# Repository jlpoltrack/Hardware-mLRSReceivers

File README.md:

# Hardware-mLRSReceivers

[mLRS](https://github.com/olliw42/mLRS) receiver boards with CAN, designed in KiCad 10.

| Board | What it is |
|---|---|
| <br>[F1-CAN-Receiver](F1-CAN-Receiver) | STM32F103 + dual E28 (SX1281), 2.4 GHz CAN |
| <br>[RP-mLRS](RP-mLRS) | RP2354A + NiceRF LR2021, CAN or CAN FD, USB-C |

Each board folder has its KiCad project, schematic PDF, renders and JLCPCB production files.

## License

[MIT](LICENSE)

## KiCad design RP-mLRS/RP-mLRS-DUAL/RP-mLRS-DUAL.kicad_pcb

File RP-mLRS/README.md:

# RP-mLRS

An [mLRS](https://github.com/olliw42/mLRS) receiver: RP2354A, NiceRF LR2021 (Sub-GHz + 2.4 GHz), two GH-compatible
CAN connectors and USB-C.

One PCB, [`RP-mLRS-DUAL/`](RP-mLRS-DUAL), takes either CAN interface, chosen at assembly:

| Build | CAN interface | Fit | Production files |
|---|---|---|---|
| CANFD | MCP251863 controller + transceiver (SPI0) | U5 | `production-canfd/` |
| CAN | [can2040](https://github.com/KevinOConnor/can2040) (PIO) + SN65HVD230 | U7 | `production-can/` |

## Connectors

**J2, J3 CAN** (CJT A1257WR-S-4P, JST-GH compatible, in parallel): 1 +5V, 2 CANH, 3 CANL, 4 GND.
Bridge **JP1** for 120 Ω termination at a bus end.

**J1 USB-C**: power (through a Schottky) and firmware.

**Test pads**: top C / G / D = SWCLK / GND / SWDIO; bottom TX / RX = UART1, TX1 = UART0 TX, 5V, G.

## Assembly

JLC assembles the top side. U4 (LR2021), C23 and C24 are on the bottom, marked DNP, and soldered by hand.

## Docs

- [docs/FIRMWARE.md](docs/FIRMWARE.md): GPIO map and firmware notes
- [docs/COST-REDUCED.md](docs/COST-REDUCED.md): CAN-build cost notes

## License

[MIT](../LICENSE)

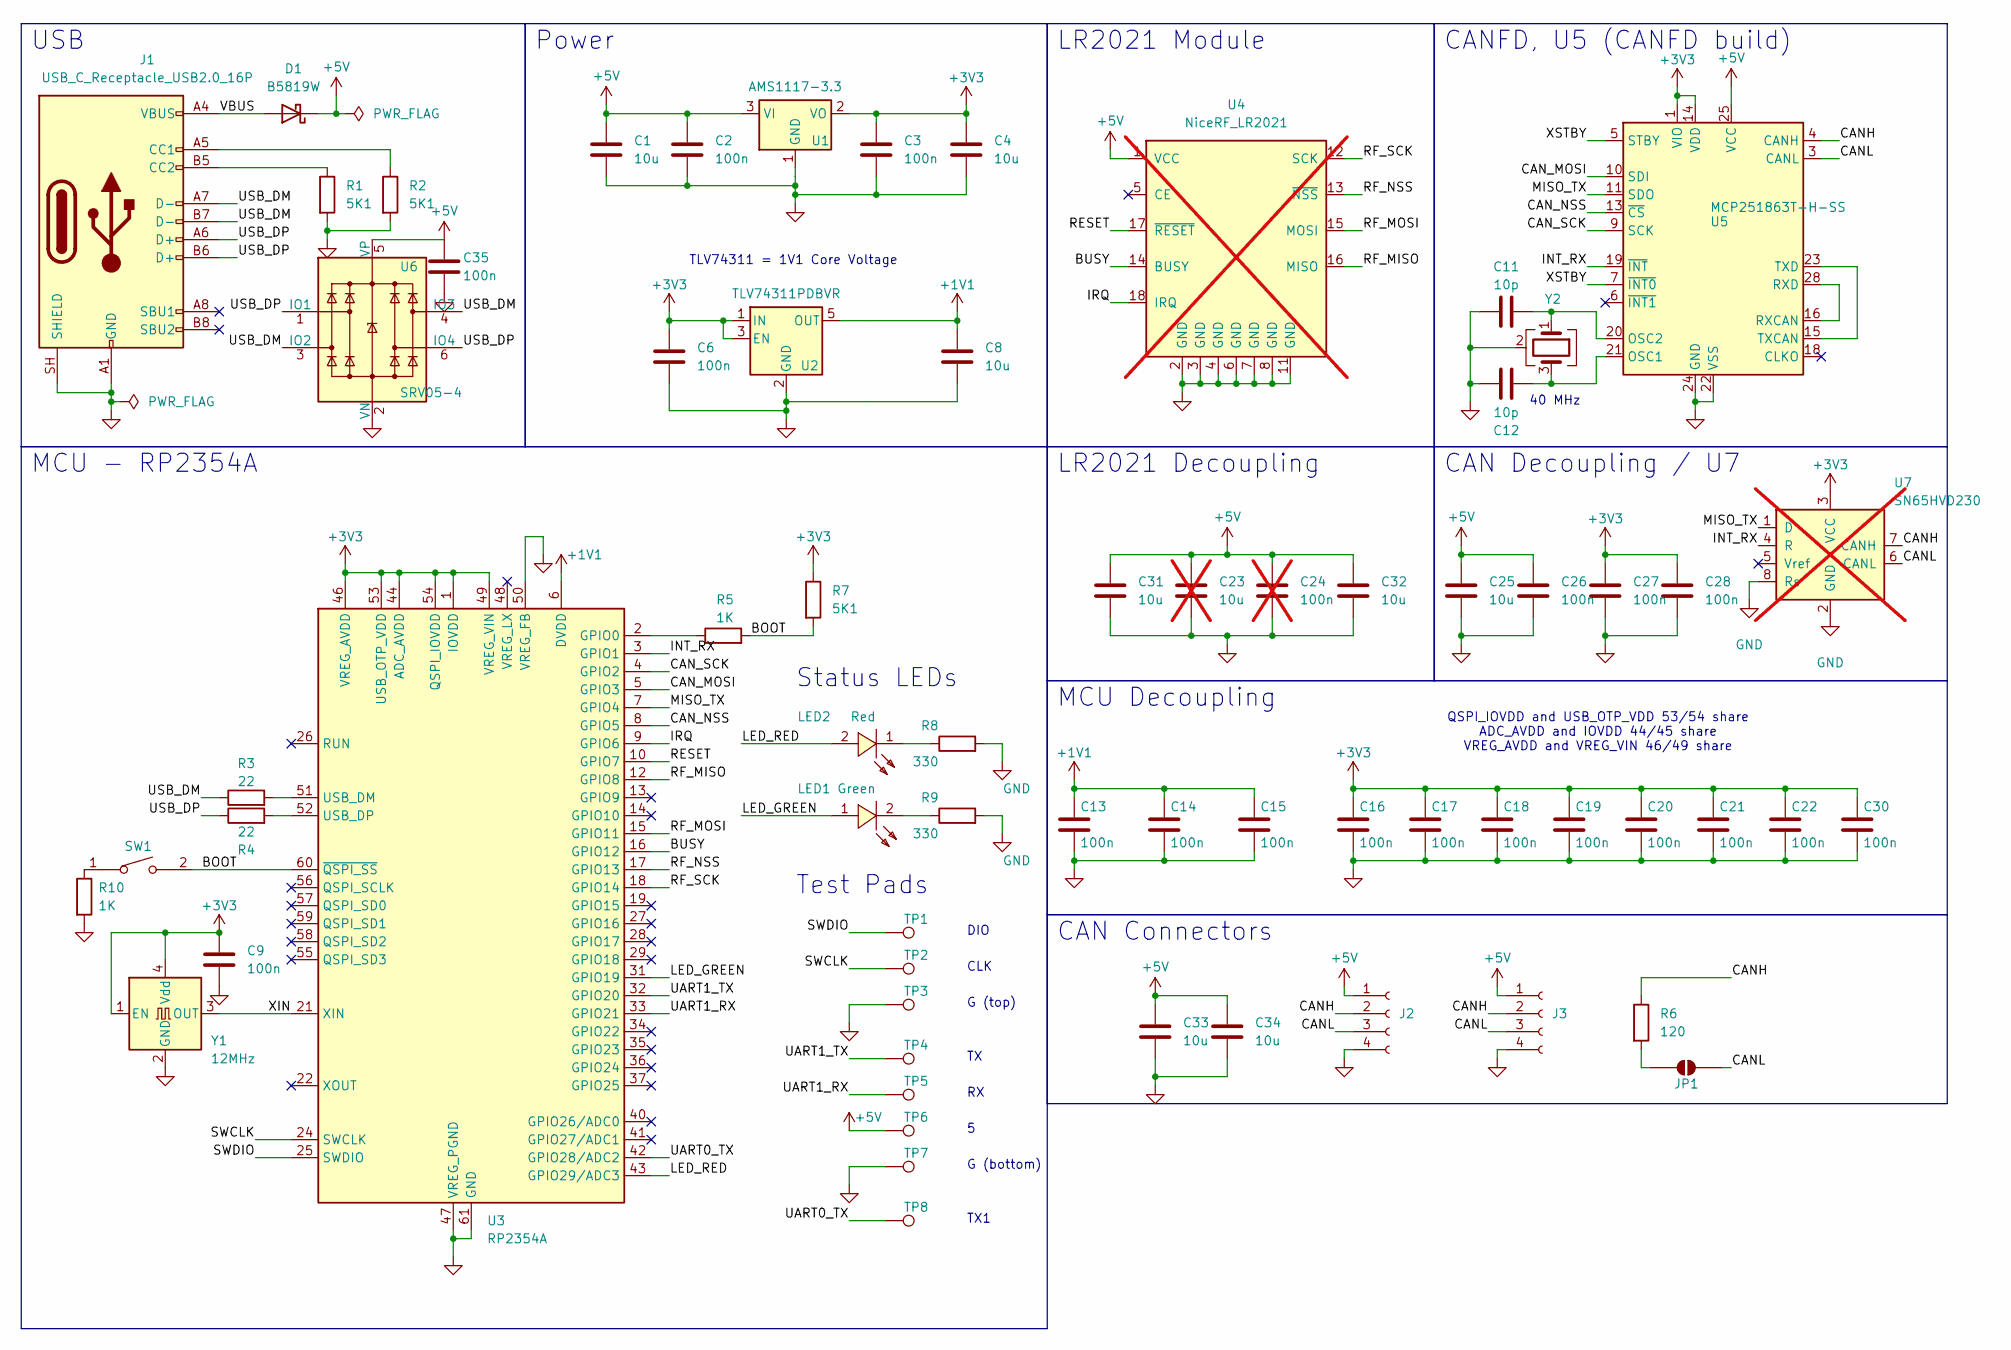
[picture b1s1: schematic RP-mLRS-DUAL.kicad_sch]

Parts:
C1, C4, C8, C25, C31, C32, C33, C34: 10u; C_0603_1608Metric; LCSC C96446
C2, C26, C35: 100n; C_0402_1005Metric; LCSC C307331
C3, C6, C9, C13, C14, C15, C16, C17, C18, C19, C20, C21, C22, C27, C28, C30: 100n; C_0402_1005Metric; LCSC C1525
C11, C12: 10p; C_0402_1005Metric; LCSC C32949
C23: 10u; C_0603_1608Metric_Pad1.08x0.95mm_HandSolder; LCSC C96446; not fitted
C24: 100n; C_0603_1608Metric_Pad1.08x0.95mm_HandSolder; LCSC C14663; not fitted
D1: B5819W; D_SOD-123; LCSC C8598
J1: USB_C_Receptacle_USB2.0_16P; USB_C_Receptacle_HH_16P_Y495; LCSC C52209111
J2, J3: Conn_01x04_Socket; CJT_A1257WR-S-4P_1x04_P1.25mm_Horizontal; LCSC C225127
JP1: SolderJumper_2_Open; SolderJumper-2_P1.3mm_Open_TrianglePad1.0x1.5mm
LED1: Green; LED0805-R-RD_NoSilk; MPN KT-0805G; LCSC Part C2297
LED2: Red; LED0805-RD_NoSilk; MPN FC-2012HRK-620D; LCSC Part C84256
R1, R2, R7: 5K1; R_0402_1005Metric; LCSC C25905
R3, R4: 22; R_0402_1005Metric; LCSC C25092
R5, R10: 1K; R_0402_1005Metric; LCSC C11702
R6: 120; R_0402_1005Metric_Pad0.72x0.64mm_HandSolder; LCSC C25079
R8, R9: 330; R_0402_1005Metric; LCSC C25104
SW1: TS-1088-AR02016; SW-SMD_L3.9-W3.0-P4.45; MPN TS-1088-AR02016; LCSC Part C720477
TP1, TP2, TP3, TP4, TP5, TP6, TP7, TP8: TestPoint; TestPoint_Pad_2.0x2.0mm
U1: AMS1117-3.3; SOT-223-3_TabPin2; LCSC C6186
U2: TLV74311PDBVR; SOT-23-5; LCSC C485147
U3: RP2354A; QFN-60-1EP_7x7mm_P0.4mm_EP3.4x3.4mm_ThermalVias; LCSC C41378174
U4: NiceRF_LR2021; NiceRF_LR2021_NoSilk; not fitted
U5: MCP251863T-H-SS; SSOP-28_5.3x10.2mm_P0.65mm; LCSC C5226885
U6: SRV05-4; SRV05-4_SOT-23-6; LCSC C85364
U7: SN65HVD230; SOIC-8_3.9x4.9mm_P1.27mm; LCSC C12084; not fitted
Y1: 12MHz; Oscillator_SMD_YXC_YSO110TR-4Pin_3.2x2.5mm; LCSC C5280582
Y2: Crystal_GND24; Crystal_SMD_2016-4Pin_2.0x1.6mm; LCSC C20623609

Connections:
+1V1: C8.1, C13.1, C14.1, C15.1, U2.5 (OUT), U3.6 (DVDD), U3.23 (DVDD), U3.39 (DVDD)
+3V3: C3.1, C4.1, C6.1, C9.1, C16.1, C17.1, C18.1, C19.1, C20.1, C21.1, C22.1, C27.1, C28.1, C30.1, R7.1, U1.2 (VO), U2.1 (IN), U2.3 (EN), U3.1 (IOVDD), U3.11 (IOVDD), U3.20 (IOVDD), U3.30 (IOVDD), U3.38 (IOVDD), U3.44 (ADC_AVDD), U3.45 (IOVDD), U3.46 (VREG_AVDD), U3.49 (VREG_VIN), U3.53 (USB_OTP_VDD), U3.54 (QSPI_IOVDD), U5.1 (VIO), U5.14 (VDD), U7.3 (VCC), Y1.1 (EN), Y1.4 (Vdd)
+5V: C1.1, C2.1, C23.1, C24.1, C25.1, C26.1, C31.1, C32.1, C33.1, C34.1, C35.1, D1.1 (K), J2.1, J3.1, TP6.1 (1_1), U1.3 (VI), U4.1 (VCC), U5.25 (VCC), U6.5 (VP)
/BOOT: R5.2, R7.2, SW1.2, U3.60 (~QSPI_SS)
/BUSY: U3.16 (GPIO12), U4.14 (BUSY)
/CANH: J2.2, J3.2, R6.1, U5.4 (CANH), U7.7 (CANH)
/CANL: J2.3, J3.3, JP1.1 (A), U5.3 (CANL), U7.6 (CANL)
/CAN_MOSI: U3.5 (GPIO3), U5.10 (SDI)
/CAN_NSS: U3.8 (GPIO5), U5.13 (~CS)
/CAN_SCK: U3.4 (GPIO2), U5.9 (SCK)
/INT_RX: U3.3 (GPIO1), U5.19 (~INT), U7.4 (R)
/IRQ: U3.9 (GPIO6), U4.18 (IRQ)
/LED_GREEN: LED1.1 (A), U3.31 (GPIO19)
/LED_RED: LED2.2 (+), U3.43 (GPIO29/ADC3)
/MISO_TX: U3.7 (GPIO4), U5.11 (SDO), U7.1 (D)
/RESET: U3.10 (GPIO7), U4.17 (~RESET)
/RF_MISO: U3.12 (GPIO8), U4.16 (MISO)
/RF_MOSI: U3.15 (GPIO11), U4.15 (MOSI)
/RF_NSS: U3.17 (GPIO13), U4.13 (~NSS)
/RF_SCK: U3.18 (GPIO14), U4.12 (SCK)
/SWCLK: TP2.1 (1_1), U3.24 (SWCLK)
/SWDIO: TP1.1 (1_1), U3.25 (SWDIO)
/UART0_TX: TP8.1 (1_1), U3.42 (GPIO28/ADC2)
/UART1_RX: TP5.1 (1_1), U3.33 (GPIO21)
/UART1_TX: TP4.1 (1_1), U3.32 (GPIO20)
/USB_DM: J1.A7 (D-), J1.B7 (D-), R3.1, U6.3 (IO2), U6.4 (IO3)
/USB_DP: J1.A6 (D+), J1.B6 (D+), R4.1, U6.1 (IO1), U6.6 (IO4)
/VBUS: D1.2 (A), J1.A4 (VBUS), J1.A9 (VBUS), J1.B4 (VBUS), J1.B9 (VBUS)
/XIN: U3.21 (XIN), Y1.3 (OUT)
/XSTBY: U5.5 (STBY), U5.7 (~INT0)
GND: C1.2, C2.2, C3.2, C4.2, C6.2, C8.2, C9.2, C11.1, C12.2, C13.2, C14.2, C15.2, C16.2, C17.2, C18.2, C19.2, C20.2, C21.2, C22.2, C23.2, C24.2, C25.2, C26.2, C27.2, C28.2, C30.2, C31.2, C32.2, C33.2, C34.2, C35.2, J1.A1 (GND), J1.A12 (GND), J1.B1 (GND), J1.B12 (GND), J1.SH (SHIELD), J2.4, J3.4, R1.2, R2.2, R8.2, R9.2, R10.2, TP3.1 (1_1), TP7.1 (1_1), U1.1 (GND), U2.2 (GND), U3.47 (VREG_PGND), U3.50 (VREG_FB), U3.61 (GND), U4.2 (GND), U4.3 (GND), U4.4 (GND), U4.6 (GND), U4.7 (GND), U4.8 (GND), U4.11 (GND), U5.22 (VSS), U5.24 (GND), U6.2 (VN), U7.2 (GND), U7.8 (Rs), Y1.2 (GND), Y2.2 (G), Y2.4 (G)
unnamed: J1.A5 (CC1), R2.1
unnamed: J1.B5 (CC2), R1.1
unnamed: JP1.2 (B), R6.2
unnamed: LED1.2 (K), R9.1
unnamed: LED2.1 (-), R8.1
unnamed: R10.1, SW1.1
unnamed: R5.1, U3.2 (GPIO0)
unnamed: R3.2, U3.51 (USB_DM)
unnamed: R4.2, U3.52 (USB_DP)
unnamed: C12.1, U5.21 (OSC1), Y2.3
unnamed: C11.2, U5.20 (OSC2), Y2.1
unnamed: U5.16 (RXCAN), U5.28 (RXD)
unnamed: U5.15 (TXCAN), U5.23 (TXD)

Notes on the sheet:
Power
QSPI_IOVDD and USB_OTP_VDD 53/54 share ADC_AVDD and IOVDD 44/45 share VREG_AVDD and VREG_VIN 46/49 share
CANFD, U5 (CANFD build)
TLV74311 = 1V1 Core Voltage
40 MHz
LR2021 Module
CAN Decoupling / U7
MCU - RP2354A
CAN Connectors
MCU Decoupling
USB
LR2021 Decoupling
Status LEDs
Test Pads
DIO
CLK
G (top)
G (bottom)
TX1

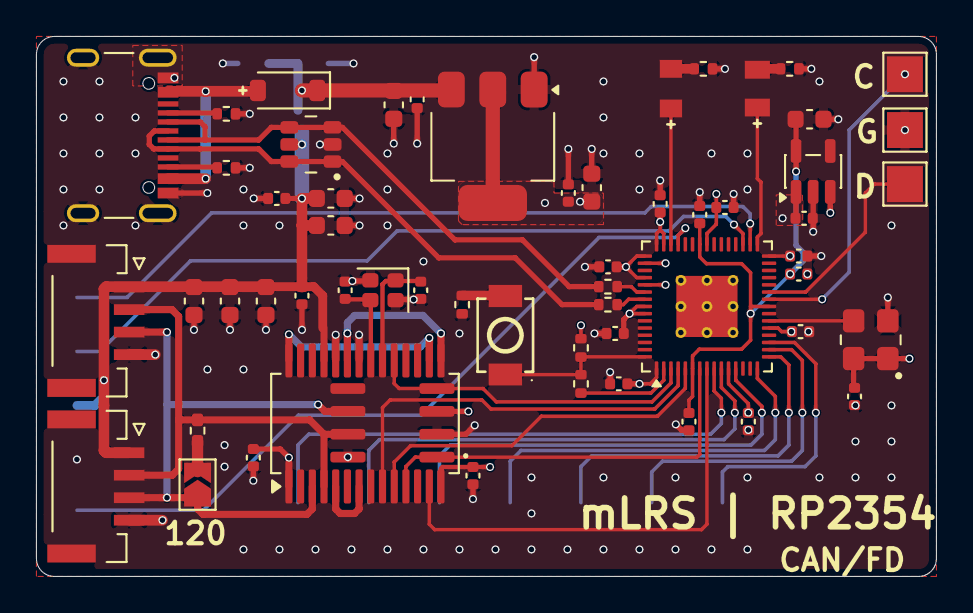
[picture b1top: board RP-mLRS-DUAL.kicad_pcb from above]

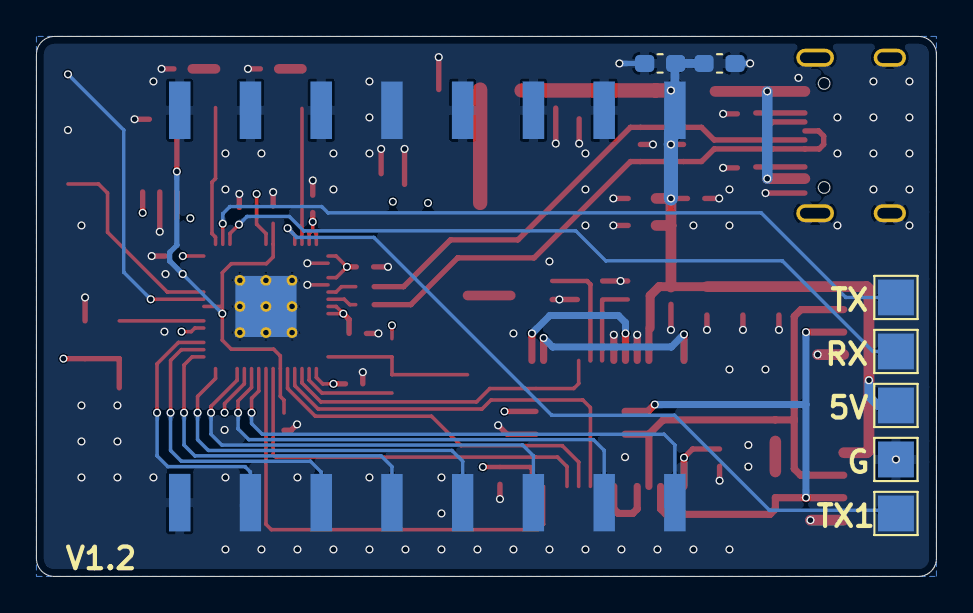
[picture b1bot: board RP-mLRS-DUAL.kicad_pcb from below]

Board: 4 copper layers, 50.0 x 30.0 mm, 68 parts (8 on the bottom side), 44 nets.

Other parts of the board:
LOGO1: mLRS title
LOGO2: title

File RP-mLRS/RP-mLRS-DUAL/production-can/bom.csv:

Designator,Footprint,Quantity,Value,LCSC Part #
"C1, C25, C31, C32, C33, C34, C4, C8",0603,8,10u,C96446
"C11, C12",0402,2,10p,C32949
"C13, C14, C15, C16, C17, C18, C19, C20, C21, C22, C27, C28, C3, C30, C6, C9",0402,16,100n,C1525
"C2, C26, C35",0402,3,100n,C307331
D1,D_SOD-123,1,B5819W,C8598
J1,USB_C_Receptacle_HH_16P_Y495,1,USB_C_Receptacle_USB2.0_16P,C52209111
"J2, J3",CJT_A1257WR-S-4P_1x04_P1.25mm_Horizontal,2,Conn_01x04_Socket,C225127
LED1,LED0805-R-RD_NoSilk,1,Green,C2297
LED2,LED0805-RD_NoSilk,1,Red,C84256
"R1, R2, R7",0402,3,5K1,C25905
"R10, R5",0402,2,1K,C11702
"R3, R4",0402,2,22,C25092
R6,0402,1,120,C25079
"R8, R9",0402,2,330,C25104
SW1,SW-SMD_L3.9-W3.0-P4.45,1,TS-1088-AR02016,C720477
U1,SOT-223-3_TabPin2,1,AMS1117-3.3,C6186
U2,SOT-23-5,1,TLV74311PDBVR,C485147
U3,QFN-60-1EP_7x7mm_P0.4mm_EP3.4x3.4mm_ThermalVias,1,RP2354A,C41378174
U6,SRV05-4_SOT-23-6,1,SRV05-4,C85364
U7,SOIC-8_3.9x4.9mm_P1.27mm,1,SN65HVD230,C12084
Y1,Oscillator_SMD_YXC_YSO110TR-4Pin_3.2x2.5mm,1,12MHz,C5280582
Y2,Crystal_SMD_2016-4Pin_2.0x1.6mm,1,Crystal_GND24,C20623609

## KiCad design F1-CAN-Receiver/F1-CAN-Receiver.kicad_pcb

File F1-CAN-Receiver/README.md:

# F1-CAN-Receiver

An [mLRS](https://github.com/olliw42/mLRS) 2.4 GHz CAN receiver: STM32F103C8T6, two E28-2G4M27S (SX1281) for
diversity, and an SN65HVD230 CAN transceiver, powered from the CAN 5 V. Based on Olli's dual-E28 board02.

## Connectors

**J1, J2 CAN** (CJT A1257WR-S-4P, JST-GH compatible, in parallel): 1 5V, 2 CAN_H, 3 CAN_L, 4 GND. Close **JP1** to terminate.

**Test pads** (bottom): UART1 (5V, TX, RX, G; also the ROM bootloader, hold BOOT0 at power-up), UART2 OUT, SWD, DBG.

## Assembly

JLC assembles the top side. M1 (top), M2 (bottom), C18 and C19 are DNP and soldered by hand; leave M2 off for a single radio.

## Docs

[docs/design.md](docs/design.md): design decisions, pin map, BOM and firmware notes.

## License

[MIT](../LICENSE)

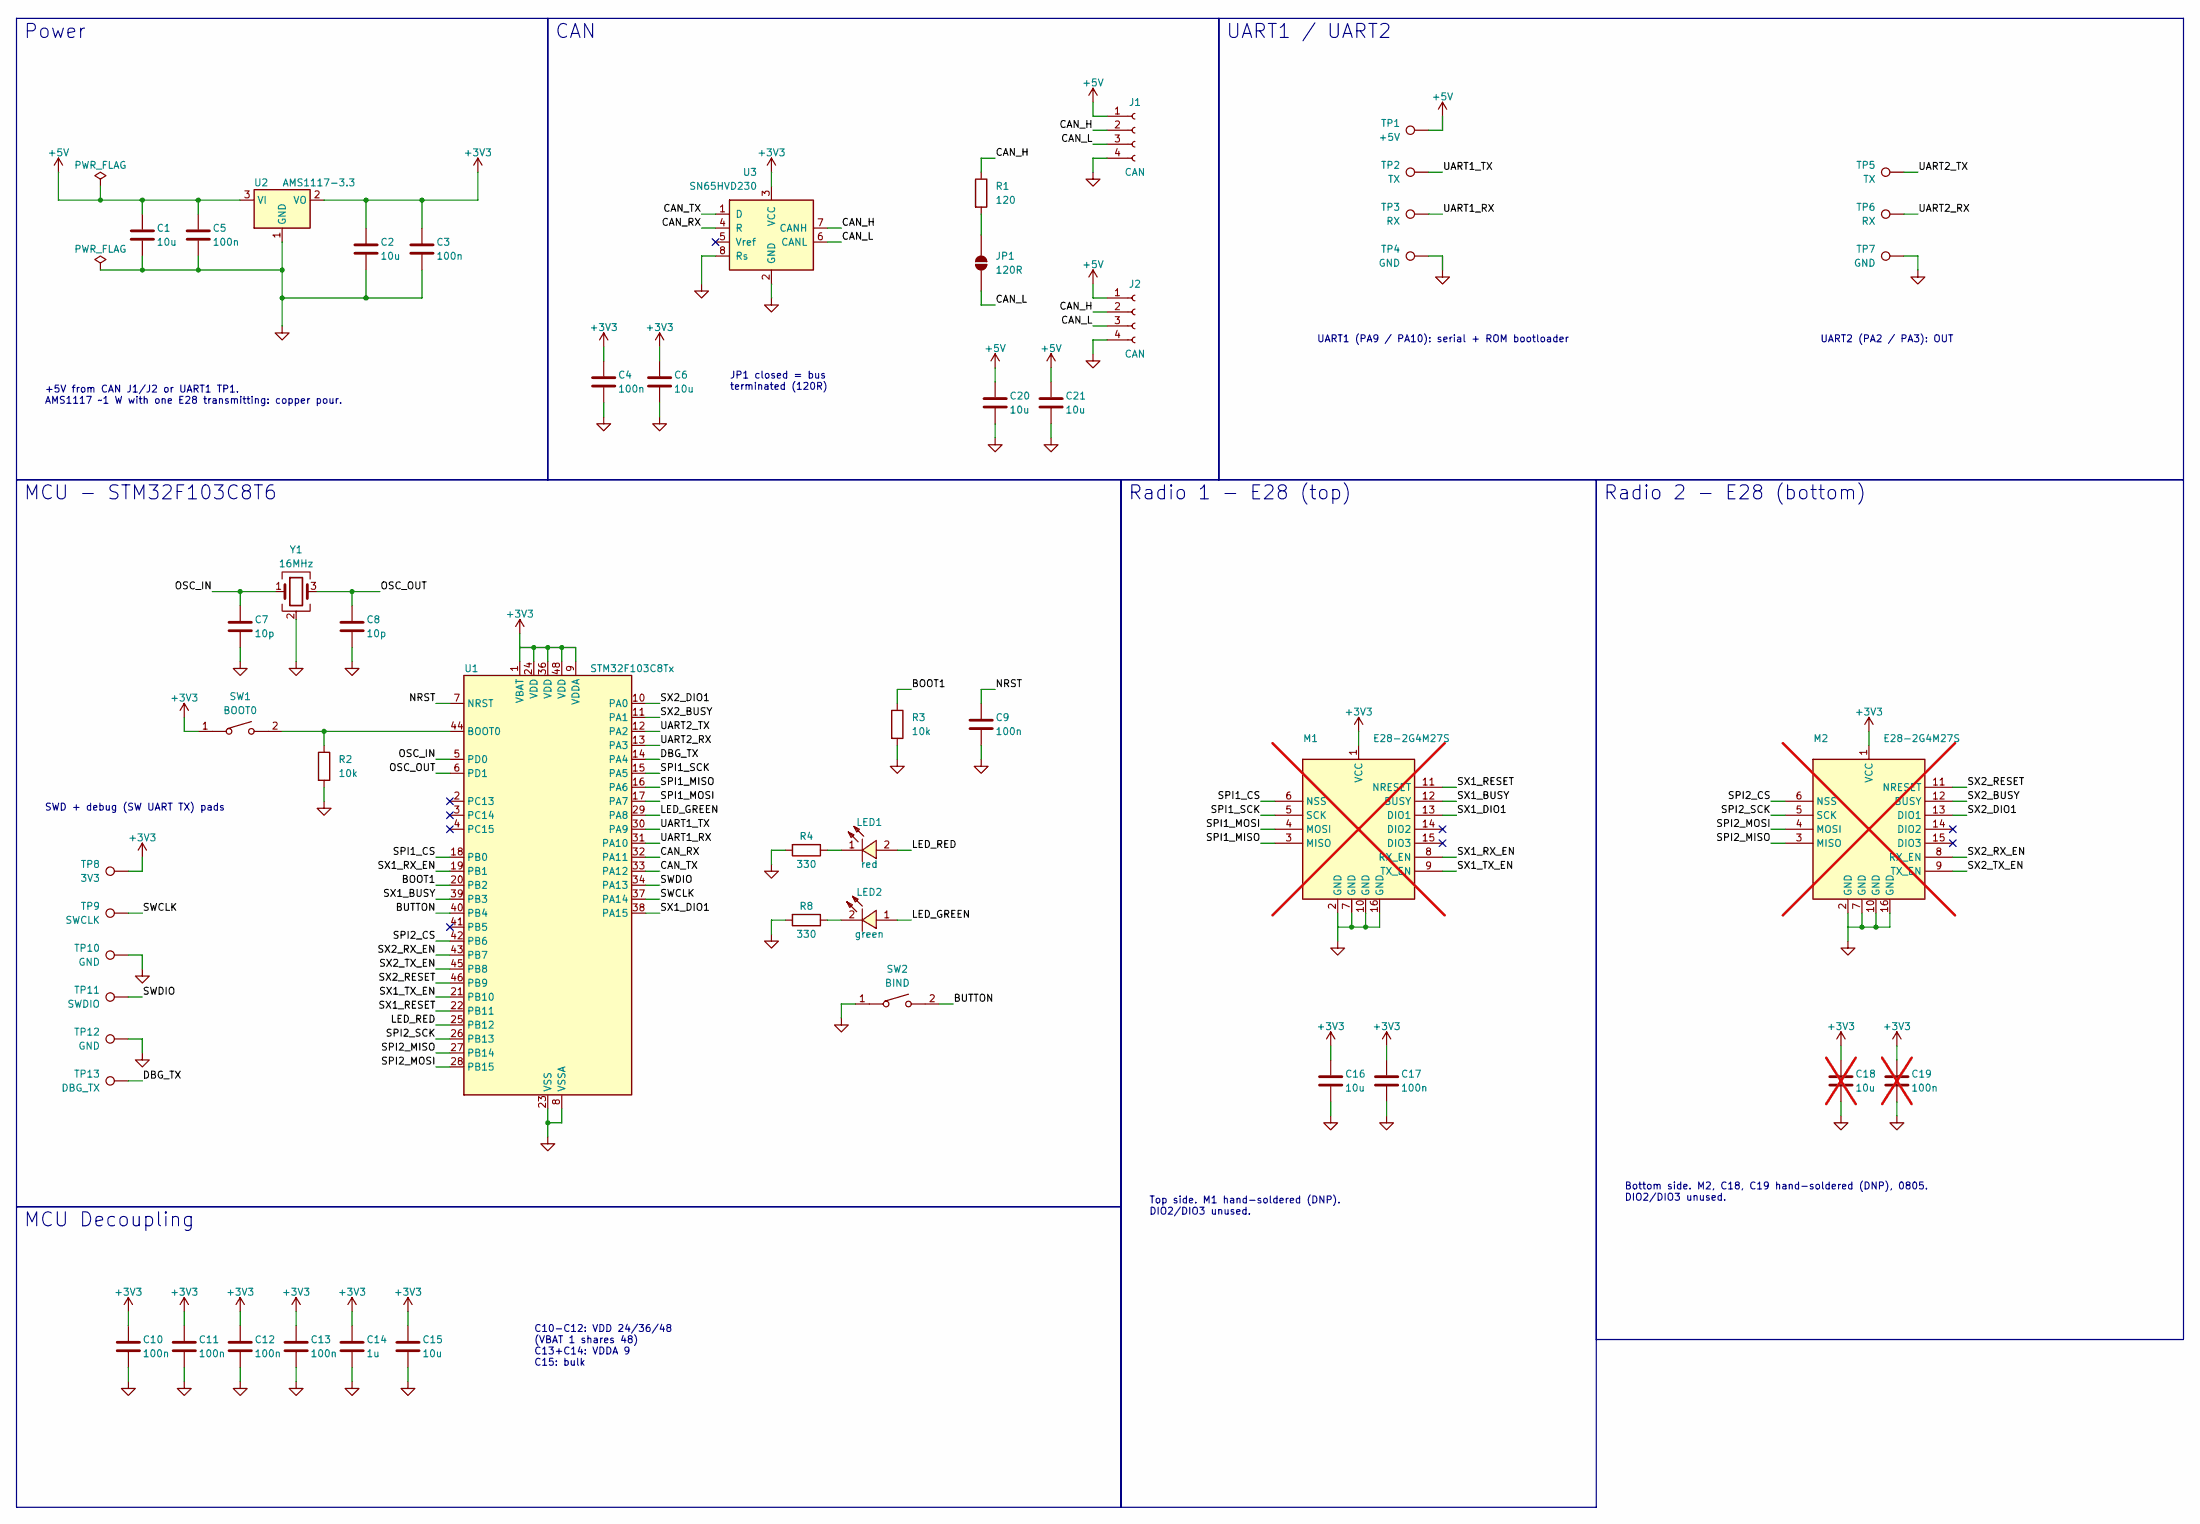
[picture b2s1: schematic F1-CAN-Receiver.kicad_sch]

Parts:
C1, C2, C6, C15, C16, C20, C21: 10u; C_0603_1608Metric; LCSC C96446
C3, C4, C5, C9, C10, C11, C12, C13, C17: 100n; C_0402_1005Metric; LCSC C307331
C7, C8: 10p; C_0402_1005Metric; LCSC C32949
C14: 1u; C_0402_1005Metric; LCSC C52923
C18: 10u; C_0805_2012Metric_Pad1.18x1.45mm_HandSolder; LCSC C15850; not fitted
C19: 100n; C_0805_2012Metric_Pad1.18x1.45mm_HandSolder; LCSC C49678; not fitted
J1, J2: CAN; CJT_A1257WR-S-4P_1x04_P1.25mm_Horizontal; LCSC C225127
JP1: 120R; SolderJumper-2_P1.3mm_Open_TrianglePad1.0x1.5mm
LED1: red; LED0805-RD_NoSilk; MPN NCD0805R1; LCSC C84256
LED2: green; LED0805-R-RD_NoSilk; MPN KT-0805G; LCSC C2297
M1, M2: E28-2G4M27S; LCSC C411312; not fitted
R1: 120; R_0402_1005Metric_Pad0.72x0.64mm_HandSolder; LCSC C25079
R2, R3: 10k; R_0402_1005Metric; LCSC C25744
R4, R8: 330; R_0402_1005Metric; LCSC C25104
SW1: BOOT0; SW-SMD_L3.9-W3.0-P4.45; MPN TS-1088-AR02016; LCSC C720477
SW2: BIND; SW-SMD_L3.9-W3.0-P4.45; MPN TS-1088-AR02016; LCSC C720477
TP1: +5V; TestPoint_Pad_2.0x2.0mm
TP2, TP5: TX; TestPoint_Pad_2.0x2.0mm
TP3, TP6: RX; TestPoint_Pad_2.0x2.0mm
TP4, TP7, TP10, TP12: GND; TestPoint_Pad_2.0x2.0mm
TP8: 3V3; TestPoint_Pad_2.0x2.0mm
TP9: SWCLK; TestPoint_Pad_2.0x2.0mm
TP11: SWDIO; TestPoint_Pad_2.0x2.0mm
TP13: DBG_TX; TestPoint_Pad_2.0x2.0mm
U1: STM32F103C8Tx; LQFP-48_7x7mm_P0.5mm; LCSC C8734
U2: AMS1117-3.3; SOT-223-3_TabPin2; LCSC C6186
U3: SN65HVD230; SOIC-8_3.9x4.9mm_P1.27mm; LCSC C12084
Y1: 16MHz; Crystal_SMD_3225-4Pin_3.2x2.5mm; LCSC C13738

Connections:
+3V3: C2.1, C3.1, C4.1, C6.1, C10.1, C11.1, C12.1, C13.1, C14.1, C15.1, C16.1, C17.1, C18.1, C19.1, M1.1 (VCC), M2.1 (VCC), SW1.1, TP8.1 (1_1), U1.1 (VBAT), U1.9 (VDDA), U1.24 (VDD), U1.36 (VDD), U1.48 (VDD), U2.2 (VO), U3.3 (VCC)
+5V: C1.1, C5.1, C20.1, C21.1, J1.1, J2.1, TP1.1 (1_1), U2.3 (VI)
/BOOT1: R3.1, U1.20 (PB2)
/BUTTON: SW2.2, U1.40 (PB4)
/CAN_H: J1.2, J2.2, R1.1, U3.7 (CANH)
/CAN_L: J1.3, J2.3, JP1.1 (A), U3.6 (CANL)
/CAN_RX: U1.32 (PA11), U3.4 (R)
/CAN_TX: U1.33 (PA12), U3.1 (D)
/DBG_TX: TP13.1 (1_1), U1.14 (PA4)
/LED_GREEN: LED2.1 (A), U1.29 (PA8)
/LED_RED: LED1.2 (+), U1.25 (PB12)
/NRST: C9.1, U1.7 (NRST)
/OSC_IN: C7.1, U1.5 (PD0), Y1.1
/OSC_OUT: C8.1, U1.6 (PD1), Y1.3
/SPI1_CS: M1.6 (NSS), U1.18 (PB0)
/SPI1_MISO: M1.3 (MISO), U1.16 (PA6)
/SPI1_MOSI: M1.4 (MOSI), U1.17 (PA7)
/SPI1_SCK: M1.5 (SCK), U1.15 (PA5)
/SPI2_CS: M2.6 (NSS), U1.42 (PB6)
/SPI2_MISO: M2.3 (MISO), U1.27 (PB14)
/SPI2_MOSI: M2.4 (MOSI), U1.28 (PB15)
/SPI2_SCK: M2.5 (SCK), U1.26 (PB13)
/SWCLK: TP9.1 (1_1), U1.37 (PA14)
/SWDIO: TP11.1 (1_1), U1.34 (PA13)
/SX1_BUSY: M1.12 (BUSY), U1.39 (PB3)
/SX1_DIO1: M1.13 (DIO1), U1.38 (PA15)
/SX1_RESET: M1.11 (NRESET), U1.22 (PB11)
/SX1_RX_EN: M1.8 (RX_EN), U1.19 (PB1)
/SX1_TX_EN: M1.9 (TX_EN), U1.21 (PB10)
/SX2_BUSY: M2.12 (BUSY), U1.11 (PA1)
/SX2_DIO1: M2.13 (DIO1), U1.10 (PA0)
/SX2_RESET: M2.11 (NRESET), U1.46 (PB9)
/SX2_RX_EN: M2.8 (RX_EN), U1.43 (PB7)
/SX2_TX_EN: M2.9 (TX_EN), U1.45 (PB8)
/UART1_RX: TP3.1 (1_1), U1.31 (PA10)
/UART1_TX: TP2.1 (1_1), U1.30 (PA9)
/UART2_RX: TP6.1 (1_1), U1.13 (PA3)
/UART2_TX: TP5.1 (1_1), U1.12 (PA2)
GND: C1.2, C2.2, C3.2, C4.2, C5.2, C6.2, C7.2, C8.2, C9.2, C10.2, C11.2, C12.2, C13.2, C14.2, C15.2, C16.2, C17.2, C18.2, C19.2, C20.2, C21.2, J1.4, J2.4, M1.2 (GND), M1.7 (GND), M1.10 (GND), M1.16 (GND), M2.2 (GND), M2.7 (GND), M2.10 (GND), M2.16 (GND), R2.2, R3.2, R4.2, R8.2, SW2.1, TP4.1 (1_1), TP7.1 (1_1), TP10.1 (1_1), TP12.1 (1_1), U1.8 (VSSA), U1.23 (VSS), U1.35 (VSS), U1.47 (VSS), U2.1 (GND), U3.2 (GND), U3.8 (Rs), Y1.2 (G), Y1.4 (G)
unnamed: JP1.2 (B), R1.2
unnamed: LED1.1 (-), R4.1
unnamed: LED2.2 (K), R8.1
unnamed: R2.1, SW1.2, U1.44 (BOOT0)

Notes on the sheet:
Power
CAN
UART1 / UART2
MCU - STM32F103C8T6
MCU Decoupling
Radio 1 - E28 (top)
Radio 2 - E28 (bottom)
+5V from CAN J1/J2 or UART1 TP1. AMS1117 ~1 W with one E28 transmitting: copper pour.
JP1 closed = bus terminated (120R)
UART1 (PA9 / PA10): serial + ROM bootloader
UART2 (PA2 / PA3): OUT
SWD + debug (SW UART TX) pads
C10-C12: VDD 24/36/48 (VBAT 1 shares 48) C13+C14: VDDA 9 C15: bulk
Top side. M1 hand-soldered (DNP). DIO2/DIO3 unused.
Bottom side. M2, C18, C19 hand-soldered (DNP), 0805. DIO2/DIO3 unused.

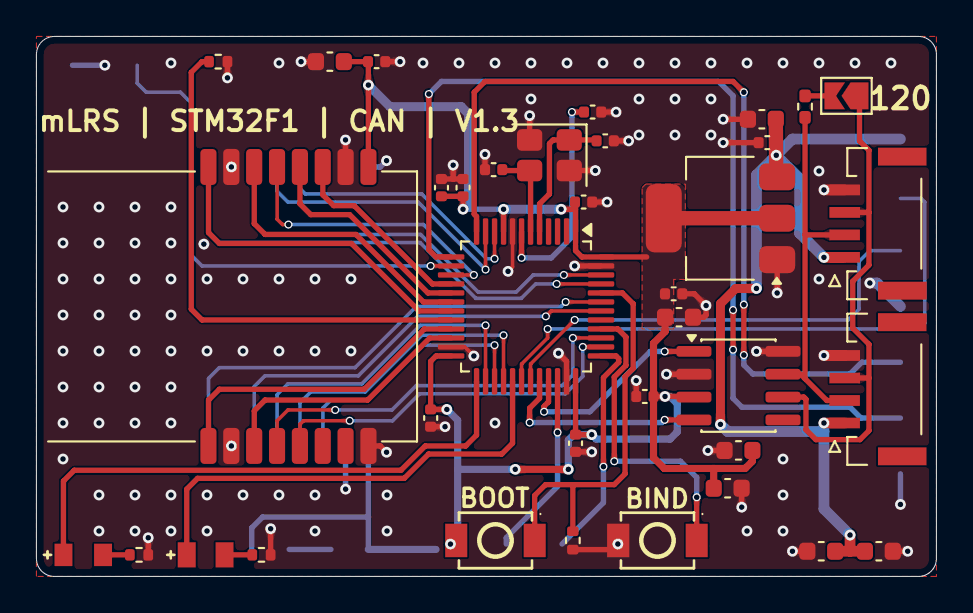
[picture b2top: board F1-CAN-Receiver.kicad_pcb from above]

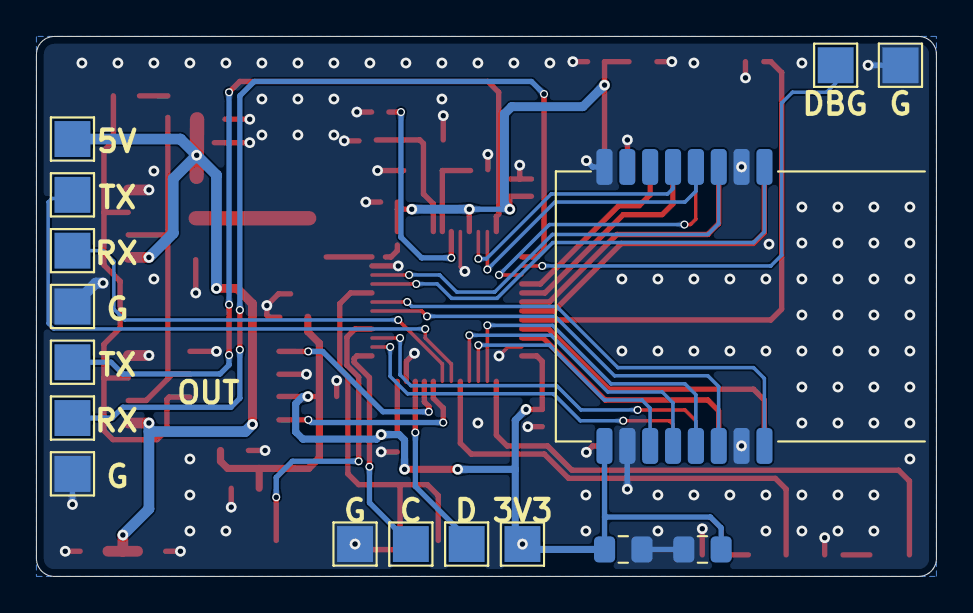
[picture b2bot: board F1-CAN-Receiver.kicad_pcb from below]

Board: 2 copper layers, 50.0 x 30.0 mm, 53 parts (16 on the bottom side), 43 nets.

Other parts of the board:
LOGO1: title

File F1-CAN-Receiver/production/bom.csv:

Designator,Footprint,Quantity,Value,LCSC Part #
"C1, C15, C16, C2, C20, C21, C6",0603,7,10u,C96446
"C10, C11, C12, C13, C17, C3, C4, C5, C9",0402,9,100n,C307331
C14,0402,1,1u,C52923
"C7, C8",0402,2,10p,C32949
"J1, J2",CJT_A1257WR-S-4P_1x04_P1.25mm_Horizontal,2,CAN,C225127
LED1,LED0805-RD_NoSilk,1,red,C84256
LED2,LED0805-R-RD_NoSilk,1,green,C2297
R1,0402,1,120,C25079
"R2, R3",0402,2,10k,C25744
"R4, R8",0402,2,330,C25104
SW1,SW-SMD_L3.9-W3.0-P4.45,1,BOOT0,C720477
SW2,SW-SMD_L3.9-W3.0-P4.45,1,BIND,C720477
U1,LQFP-48_7x7mm_P0.5mm,1,STM32F103C8Tx,C8734
U2,SOT-223-3_TabPin2,1,AMS1117-3.3,C6186
U3,SOIC-8_3.9x4.9mm_P1.27mm,1,SN65HVD230,C12084
Y1,Crystal_SMD_3225-4Pin_3.2x2.5mm,1,16MHz,C13738
